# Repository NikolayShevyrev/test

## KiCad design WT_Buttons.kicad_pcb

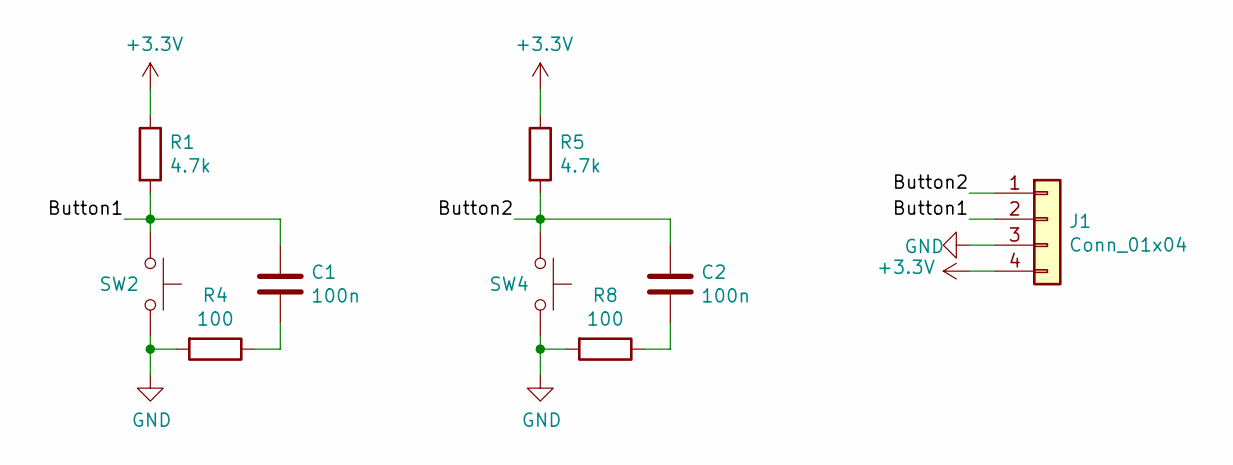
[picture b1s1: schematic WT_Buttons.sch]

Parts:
C1, C2: 100n; C_0805_2012Metric_Pad1.18x1.45mm_HandSolder
J1: Conn_01x04; PinHeader_1x04_P2.54mm_Vertical
R1, R5: 4.7k; R_0805_2012Metric_Pad1.20x1.40mm_HandSolder
R4, R8: 100; R_0805_2012Metric_Pad1.20x1.40mm_HandSolder
SW2, SW4: SW_Push; SW_PUSH_6mm_H8mm

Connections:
+3V3: J1.4, R1.1, R5.1
/Button1: C1.1, J1.2, R1.2, SW2.1
/Button2: C2.1, J1.1, R5.2, SW4.1
GND: J1.3, R4.2, R8.2, SW2.2, SW4.2
unnamed: C1.2, R4.1
unnamed: C2.2, R8.1

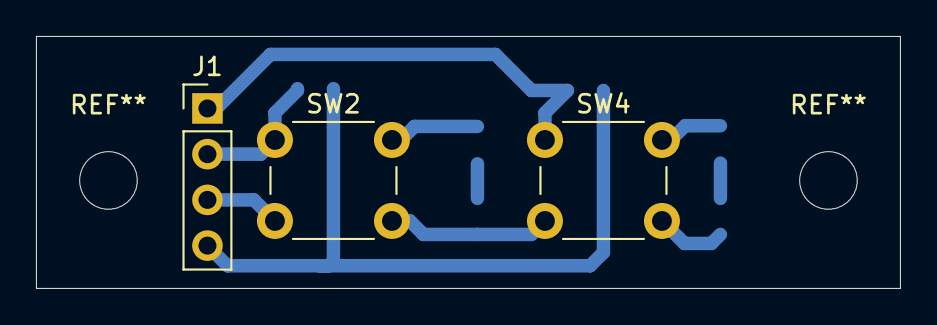
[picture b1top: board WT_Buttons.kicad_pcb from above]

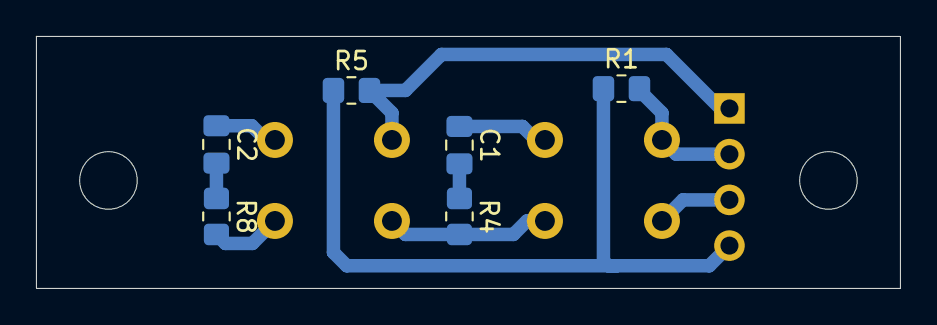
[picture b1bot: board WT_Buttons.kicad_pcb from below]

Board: 2 copper layers, 48.0 x 14.0 mm, 9 parts (6 on the bottom side), 6 nets.

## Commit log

2022-01-27 first
